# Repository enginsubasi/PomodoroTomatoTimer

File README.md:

# PomodoroTomatoTimer
Simplest tomato timer for pomodoro technique

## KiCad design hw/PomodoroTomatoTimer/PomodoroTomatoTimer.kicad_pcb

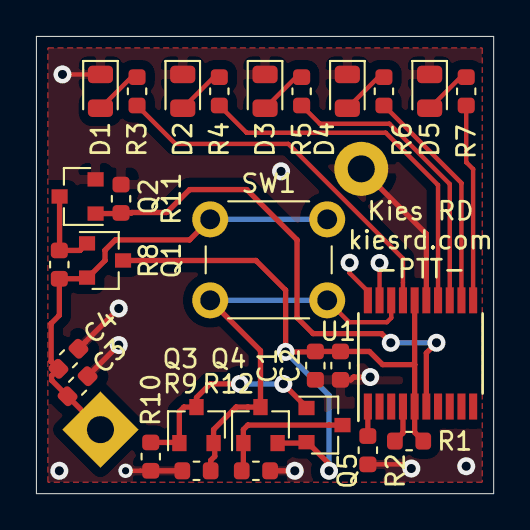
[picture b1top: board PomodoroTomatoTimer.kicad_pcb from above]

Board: 2 copper layers, 25.4 x 25.4 mm, 29 parts (1 on the bottom side), 20 nets.

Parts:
C1, C3: 100nF 0603; C_0603_1608Metric
C2, C4: 330nF 0603; C_0603_1608Metric
D1, D2, D3, D4, D5: LED; LED_0805_2012Metric
J1: Coin Cell; BatteryHolder_Keystone_103_1x20mm
Q1, Q4: BSS83P; SOT-23
Q2: 2N7002; SOT-23
Q3, Q5: BC807; SOT-23
R1, R2, R8, R9, R11: 10k 0603; R_0603_1608Metric
R3, R4, R5, R6, R7: 1k 0603; R_0603_1608Metric
R10, R12: 47k 0603; R_0603_1608Metric
SW1: SW_DPST_x2; SW_PUSH_6mm
U1: STM32F030F4Px; TSSOP-20_4.4x6.5mm_P0.65mm

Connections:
/BUTTON: Q3.2, Q4.3, R9.1, SW1.2, U1.18
/LED1: R3.2, U1.17
/LED2: R4.2, U1.14
/LED3: R5.2, U1.13
/LED4: R6.2, U1.12
/LED5: R7.2, U1.11
/POW_CTRL: Q2.1, R11.1, U1.6
GND: C1.2, C2.2, C3.2, C4.2, D1.1, D2.1, D3.1, D4.1, D5.1, J1.2, Q2.2, R2.1, R9.2, R10.2, R11.2, R12.2, U1.15
unnamed: D1.2, R3.1
unnamed: D2.2, R4.1
unnamed: D3.2, R5.1
unnamed: D4.2, R6.1
unnamed: D5.2, R7.1
unnamed: Q1.1, Q2.3, R8.2
unnamed: Q3.1, Q3.3, Q5.1, R10.1
unnamed: Q4.1, Q5.3, R12.1
unnamed: R1.1, U1.4
unnamed: R2.2, U1.1
VDD: C1.1, C2.1, Q1.3, Q4.2, Q5.2, R1.2, U1.5, U1.16
VDDA: C3.1, C4.1, J1.1, Q1.2, R8.1, SW1.1

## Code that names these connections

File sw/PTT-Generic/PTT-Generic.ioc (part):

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Mcu.Name=STM32F030F4Px
Mcu.Package=TSSOP20
Mcu.UserName=STM32F030F4Px
PA0.GPIOParameters=PinState,GPIO_Label
PA0.GPIO_Label=POW_CTRL
PA0.PinState=GPIO_PIN_SET
PA0.Signal=GPIO_Output
PA10.GPIOParameters=GPIO_Label
PA10.GPIO_Label=BUTTON
PA10.Signal=GPIO_Input
PA13.Mode=Serial_Wire
PA13.Signal=SYS_SWDIO
PA14.Mode=Serial_Wire
PA14.Signal=SYS_SWCLK
PA5.GPIOParameters=GPIO_Label
PA5.GPIO_Label=LED5
PA5.Signal=GPIO_Output
PA6.GPIOParameters=GPIO_Label
PA6.GPIO_Label=LED4
PA6.Signal=GPIO_Output
PA7.GPIOParameters=GPIO_Label
PA7.GPIO_Label=LED3
PA7.Signal=GPIO_Output
PA9.GPIOParameters=GPIO_Label
PA9.GPIO_Label=LED1
PA9.Signal=GPIO_Output
PB1.GPIOParameters=GPIO_Label
PB1.GPIO_Label=LED2
PB1.Signal=GPIO_Output
RCC.SYSCLKFreq_VALUE=8000000
board=custom

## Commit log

2019-07-16 + mcu datasheet
2019-07-16 + PTT hw init. Not ok.
2019-07-18 + Placement and routing ok.
2019-07-18 + silk screen updated
2019-07-25 + 3D Box
2019-07-25 + 3D Box v2
2019-07-26 + 3D Updated. Empty software project created
2019-07-26 + Basic sw frame
2019-07-26 + SM under development
2019-08-07 + not optimized but almost ok. Not tested on device.
2019-09-19 + v1 gerber
2019-09-19 + cubemx update
2019-09-19 + gerber
2019-09-24 + mechanical improvements
2019-09-24 + shut down function
2019-09-25 / nc
2019-10-06 + mec
2022-03-11 + FW update.
